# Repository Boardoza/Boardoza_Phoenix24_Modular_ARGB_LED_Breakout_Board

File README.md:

# Boardoza Phoenix24 Breakout Board

The **Boardoza Phoenix24** is a high-performance **addressable RGB (ARGB) LED breakout board** featuring **24 individually addressable LEDs** based on the **T3A33BRG-H9C0002X1U1930** LED chipset. It is designed to deliver vibrant, dynamic lighting effects while maintaining reliable signal integrity across complex LED chains.

Thanks to its **DIN, CIN, DOUT, and COUT** signal routing and support for **both CMOS and TTL logic levels**, Phoenix24 can be seamlessly integrated into a wide range of embedded systems. With **THT (Through-Hole)** and **SMD (Surface-Mount)** connection options, the board is suitable for both rapid prototyping and final product designs, making it ideal for **lighting installations, user interfaces, visual feedback systems, and decorative applications**.

## [Click here to purchase!](https://www.ozdisan.com/ureticiler/boardoza)
| Front Side | Back Side |
|:---:|:---:|
|  |  |

---

## Key Features

- **24 Addressable RGB LEDs:** Enables vivid, dynamic, and individually controllable lighting effects.
- **CMOS & TTL Signal Compatibility:** Ensures seamless integration with a wide range of microcontrollers and logic systems.
- **Dedicated Data & Clock Lines:** Separate DIN, CIN, DOUT, and COUT signals provide reliable signal flow and easy daisy-chaining.
- **Flexible Connection Options:** Supports both THT (Through-Hole) and SMD (Surface-Mount) connections for versatile assembly.
- **Wide Application Support:** Ideal for lighting systems, visual feedback, user interfaces, and decorative projects.

---

## Technical Specifications

**Model:** Phoenix24  
**Manufacturer:** Boardoza  
**Functions:** Addressable RGB LED Lighting Board  
**Input Voltage:** 3.3 V / 5 V  
**LED Model:** T3A33BRG-H9C0002X1U1930  
**Number of LEDs:** 24   
**LED Type:** Individually addressable RGB LEDs  
**Logic Compatibility:** TTL & CMOS  
**Data Interface:** Serial Data & Clock (DIN / CIN / DOUT / COUT)  
**Daisy-Chain Support:** Yes  
**Operating Temperature:** -40 °C to +85 °C   
**Board Dimensions:** 67.24 mm × 67.18 mm

---

## Board Pinout

### **( J1 ) Power Connector**
| Pin Number | Pin Name | Description |
|:---:|:---:|---|
| 1 | VCC | Power Supply |

### **( J2 ) Power Connector**
| Pin Number | Pin Name | Description |
|:---:|:---:|---|
| 1 | VCC | Power Supply |

### **( J3 ) Data Input**
| Pin Number | Pin Name | Description |
|:---:|:---:|---|
| 1 | DIN | Serial Data Input |

### **( J4 ) Clock Input**
| Pin Number | Pin Name | Description |
|:---:|:---:|---|
| 1 | CIN | Clock Input |

### **( J5 ) Data Output**
| Pin Number | Pin Name | Description |
|:---:|:---:|---|
| 1 | DOUT | Serial Data Output |

### **( J6 ) Clock Output**
| Pin Number | Pin Name | Description |
|:---:|:---:|---|
| 1 | COUT | Clock Output |

### **( J7 ) Ground**
| Pin Number | Pin Name | Description |
|:---:|:---:|---|
| 1 | GND | Ground |

### **( J8 ) Ground**
| Pin Number | Pin Name | Description |
|:---:|:---:|---|
| 1 | GND | Ground |

---

## Board Dimensions

---

## Step Files

[Boardoza Phoenix24.step](./assets/Phoenix24%20Step.step)

---

## Datasheet

[T3A33BRG Datasheet](./assets/Phoenix24%20Datasheet.pdf)

---

## Version History

- **V1.0.0** – Initial Release

---

## Support

- For questions or technical support, please contact **support@boardoza.com**

---

## **License**

This repository contains both hardware and software components:

### **Hardware Design**

[![CC BY-SA 4.0][cc-by-sa-shield]][cc-by-sa]

All hardware design files are licensed under [Creative Commons Attribution-ShareAlike 4.0 International License][cc-by-sa].

[cc-by-sa]: http://creativecommons.org/licenses/by-sa/4.0/
[cc-by-sa-shield]: https://img.shields.io/badge/License-CC%20BY--SA%204.0-lightgrey.svg

### **Software/Firmware**

[![BSD-3-Clause][bsd-shield]][bsd]

All software and firmware are licensed under [BSD 3-Clause License][bsd].

[bsd]: https://opensource.org/licenses/BSD-3-Clause
[bsd-shield]: https://img.shields.io/badge/License-BSD%203--Clause-blue.svg

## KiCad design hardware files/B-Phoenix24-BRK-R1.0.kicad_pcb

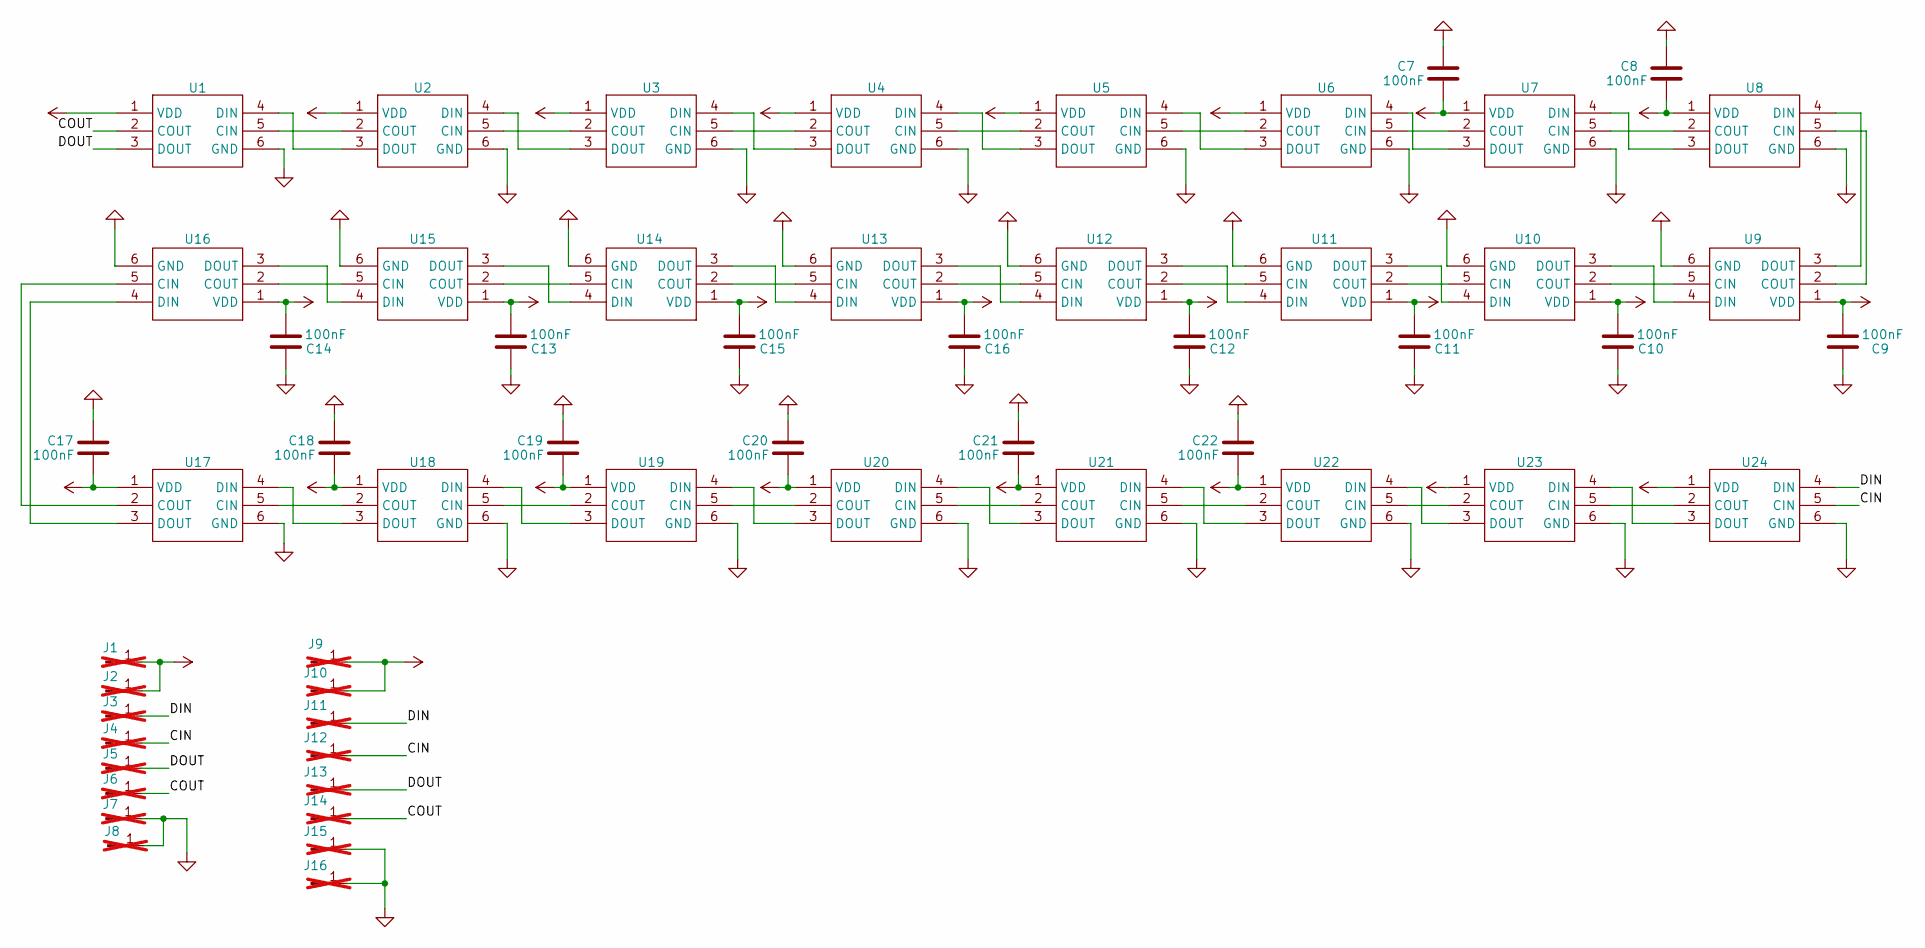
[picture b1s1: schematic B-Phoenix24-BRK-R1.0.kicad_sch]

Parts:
C7, C8, C9, C10, C11, C12, C13, C14, C15, C16, C17, C18, C19, C20, C21, C22: 100nF; C_0402_1005Metric; MPN MCF02KTB250104
J1, J2, J3, J4, J5, J6, J7, J8: Conn_01x01_Pin; PinSocket_1x01_P2.54mm_Vertical; not fitted
J9, J10, J11, J12, J13, J14, J15, J16: Conn_01x01_Pin; SolderWirePad_1x01_SMD_1x2mm; not fitted
U1, U2, U3, U4, U5, U6, U7, U8, U9, U10, U11, U12, U13, U14, U15, U16, U17, U18, U19, U20, U21, U22, U23, U24: T3A33BRG-H9C0002X1U1930_HVK; MPN T3A33BRG-H9C0002X1U1930

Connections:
/CIN: J4.1, J12.1, U24.5 (CIN)
/COUT: J6.1, J14.1, U1.2 (COUT)
/DIN: J3.1, J11.1, U24.4 (DIN)
/DOUT: J5.1, J13.1, U1.3 (DOUT)
GND: C7.1, C8.1, C9.1, C10.1, C11.1, C12.1, C13.1, C14.1, C15.1, C16.1, C17.1, C18.1, C19.1, C20.1, C21.1, C22.1, J7.1, J8.1, J15.1, J16.1, U1.6 (GND), U2.6 (GND), U3.6 (GND), U4.6 (GND), U5.6 (GND), U6.6 (GND), U7.6 (GND), U8.6 (GND), U9.6 (GND), U10.6 (GND), U11.6 (GND), U12.6 (GND), U13.6 (GND), U14.6 (GND), U15.6 (GND), U16.6 (GND), U17.6 (GND), U18.6 (GND), U19.6 (GND), U20.6 (GND), U21.6 (GND), U22.6 (GND), U23.6 (GND), U24.6 (GND)
unnamed: U1.5 (CIN), U2.2 (COUT)
unnamed: U1.4 (DIN), U2.3 (DOUT)
unnamed: U2.5 (CIN), U3.2 (COUT)
unnamed: U2.4 (DIN), U3.3 (DOUT)
unnamed: U3.5 (CIN), U4.2 (COUT)
unnamed: U3.4 (DIN), U4.3 (DOUT)
unnamed: U4.5 (CIN), U5.2 (COUT)
unnamed: U4.4 (DIN), U5.3 (DOUT)
unnamed: U5.5 (CIN), U6.2 (COUT)
unnamed: U5.4 (DIN), U6.3 (DOUT)
unnamed: U6.5 (CIN), U7.2 (COUT)
unnamed: U6.4 (DIN), U7.3 (DOUT)
unnamed: U7.5 (CIN), U8.2 (COUT)
unnamed: U7.4 (DIN), U8.3 (DOUT)
unnamed: U8.5 (CIN), U9.2 (COUT)
unnamed: U8.4 (DIN), U9.3 (DOUT)
unnamed: U10.5 (CIN), U11.2 (COUT)
unnamed: U9.5 (CIN), U10.2 (COUT)
unnamed: U10.4 (DIN), U11.3 (DOUT)
unnamed: U9.4 (DIN), U10.3 (DOUT)
unnamed: U11.5 (CIN), U12.2 (COUT)
unnamed: U11.4 (DIN), U12.3 (DOUT)
unnamed: U12.5 (CIN), U13.2 (COUT)
unnamed: U12.4 (DIN), U13.3 (DOUT)
unnamed: U13.5 (CIN), U14.2 (COUT)
unnamed: U13.4 (DIN), U14.3 (DOUT)
unnamed: U14.5 (CIN), U15.2 (COUT)
unnamed: U14.4 (DIN), U15.3 (DOUT)
unnamed: U15.5 (CIN), U16.2 (COUT)
unnamed: U15.4 (DIN), U16.3 (DOUT)
unnamed: U16.5 (CIN), U17.2 (COUT)
unnamed: U16.4 (DIN), U17.3 (DOUT)
unnamed: U17.5 (CIN), U18.2 (COUT)
unnamed: U17.4 (DIN), U18.3 (DOUT)
unnamed: U18.5 (CIN), U19.2 (COUT)
unnamed: U18.4 (DIN), U19.3 (DOUT)
unnamed: U19.5 (CIN), U20.2 (COUT)
unnamed: U19.4 (DIN), U20.3 (DOUT)
unnamed: U20.5 (CIN), U21.2 (COUT)
unnamed: U20.4 (DIN), U21.3 (DOUT)
unnamed: U21.5 (CIN), U22.2 (COUT)
unnamed: U21.4 (DIN), U22.3 (DOUT)
unnamed: U22.5 (CIN), U23.2 (COUT)
unnamed: U22.4 (DIN), U23.3 (DOUT)
unnamed: U23.5 (CIN), U24.2 (COUT)
unnamed: U23.4 (DIN), U24.3 (DOUT)
VCC: C7.2, C8.2, C9.2, C10.2, C11.2, C12.2, C13.2, C14.2, C15.2, C16.2, C17.2, C18.2, C19.2, C20.2, C21.2, C22.2, J1.1, J2.1, J9.1, J10.1, U1.1 (VDD), U2.1 (VDD), U3.1 (VDD), U4.1 (VDD), U5.1 (VDD), U6.1 (VDD), U7.1 (VDD), U8.1 (VDD), U9.1 (VDD), U10.1 (VDD), U11.1 (VDD), U12.1 (VDD), U13.1 (VDD), U14.1 (VDD), U15.1 (VDD), U16.1 (VDD), U17.1 (VDD), U18.1 (VDD), U19.1 (VDD), U20.1 (VDD), U21.1 (VDD), U22.1 (VDD), U23.1 (VDD), U24.1 (VDD)

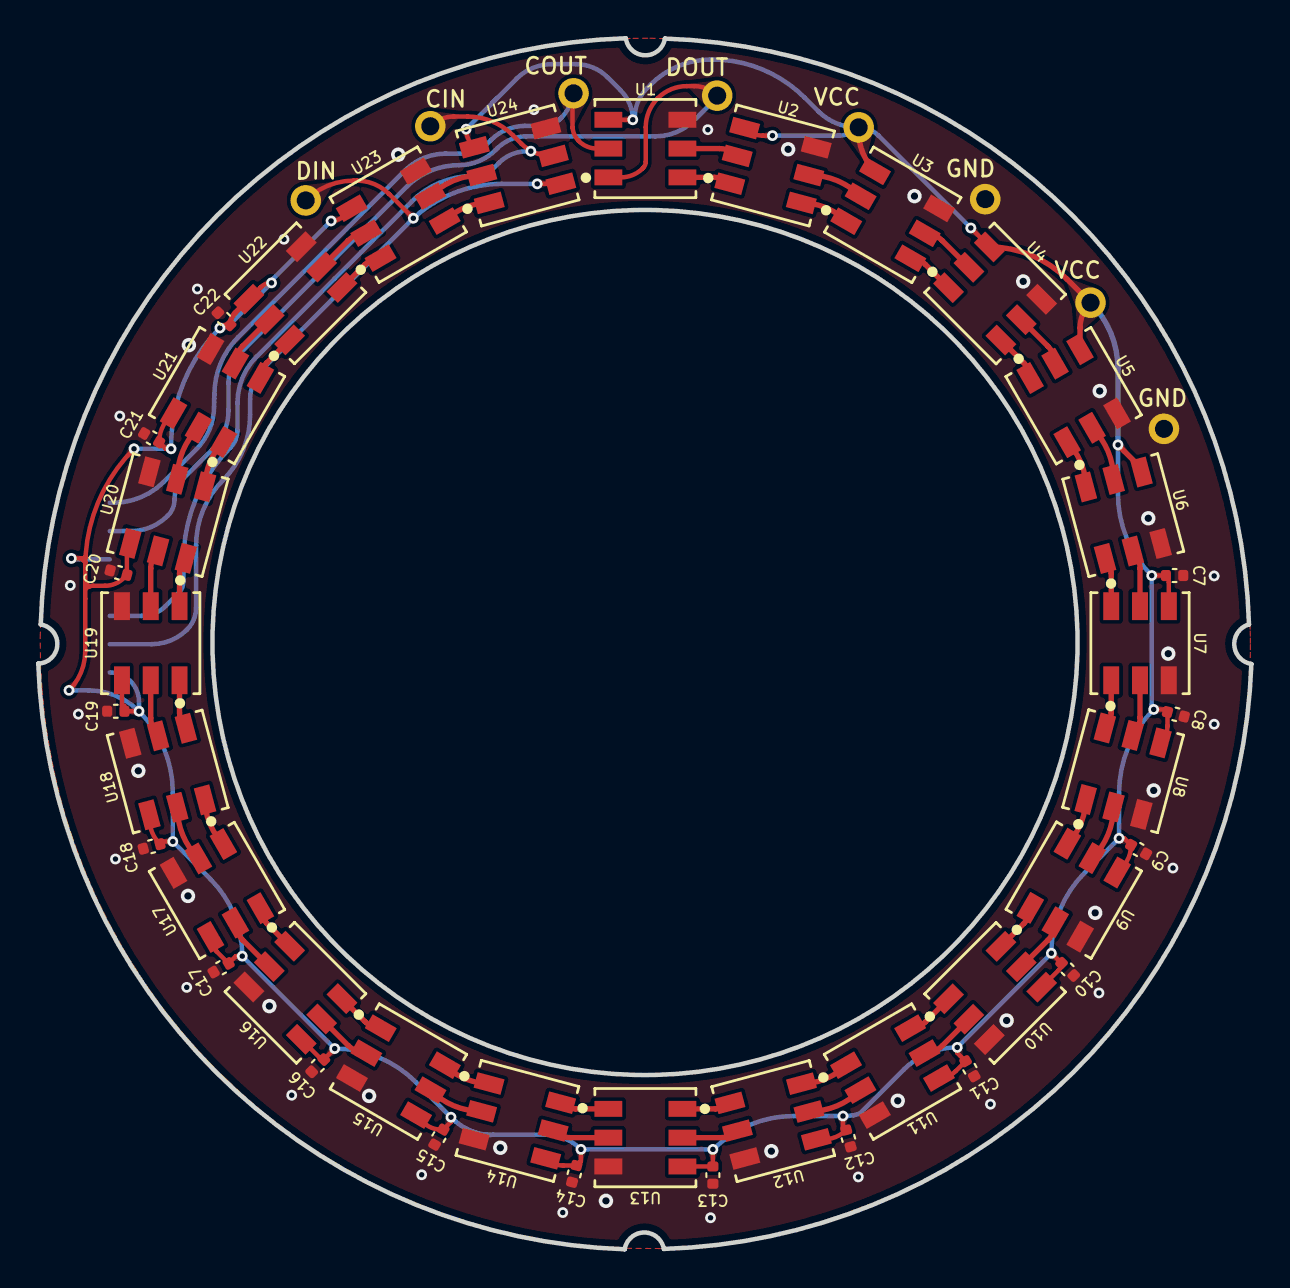
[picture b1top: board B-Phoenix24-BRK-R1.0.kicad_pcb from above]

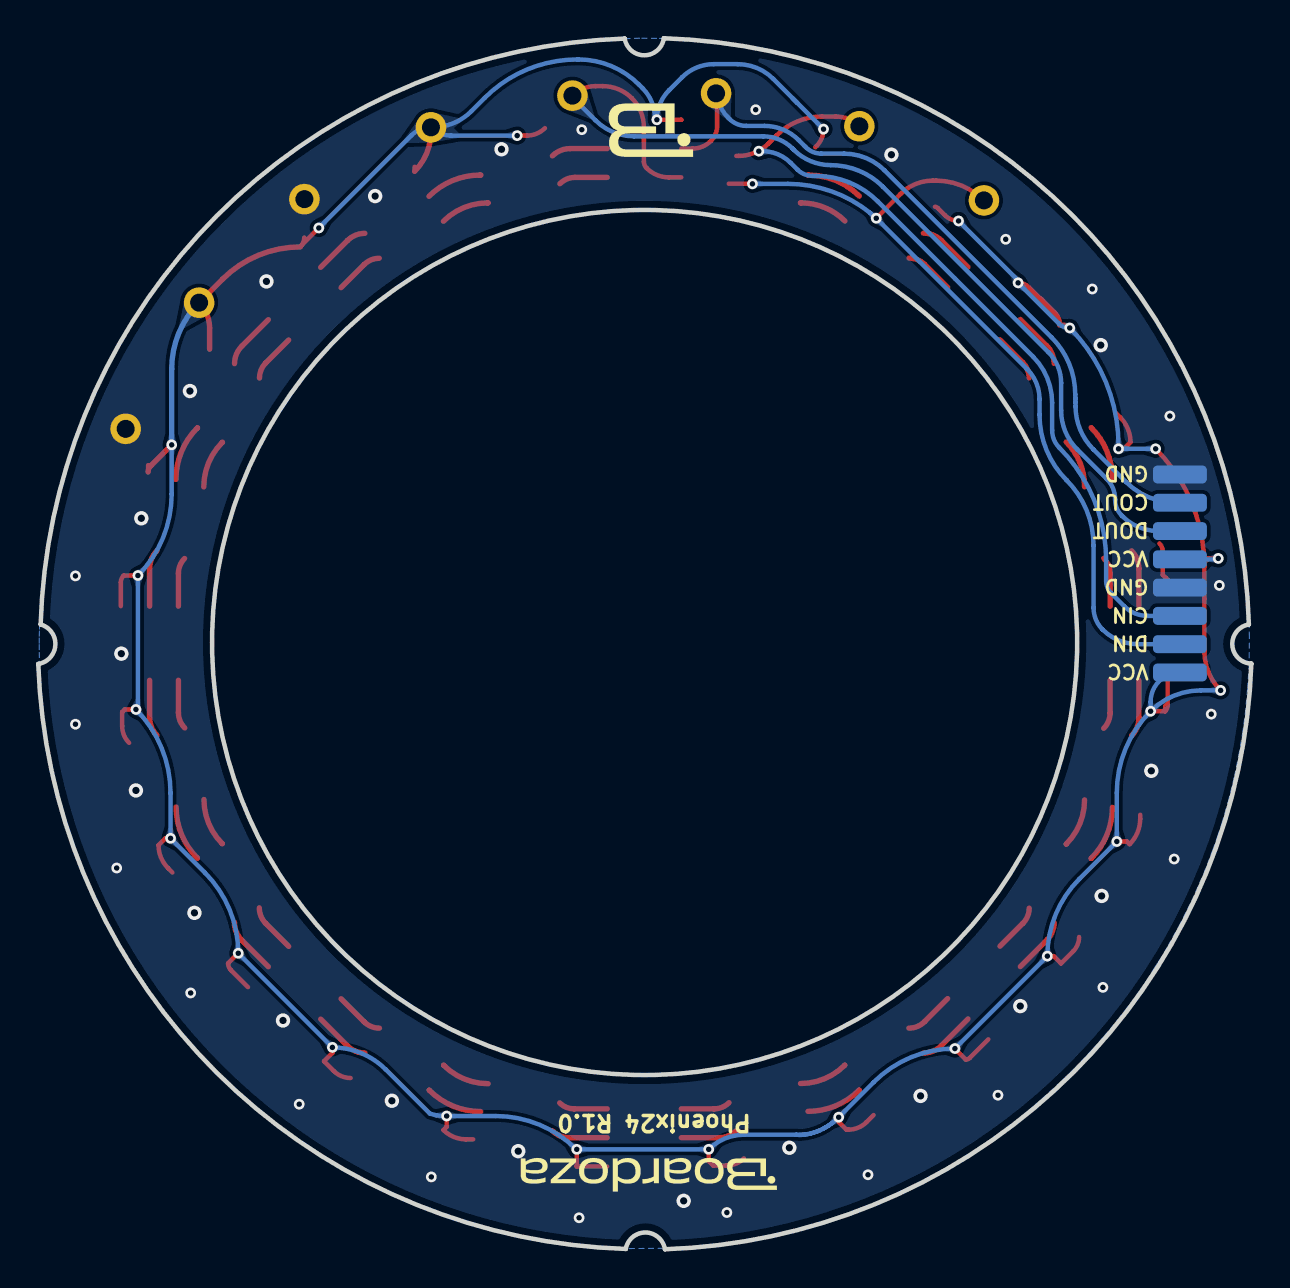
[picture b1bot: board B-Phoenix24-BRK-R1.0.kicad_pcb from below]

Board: 2 copper layers, 67.4 x 67.3 mm, 56 parts (8 on the bottom side), 52 nets.
